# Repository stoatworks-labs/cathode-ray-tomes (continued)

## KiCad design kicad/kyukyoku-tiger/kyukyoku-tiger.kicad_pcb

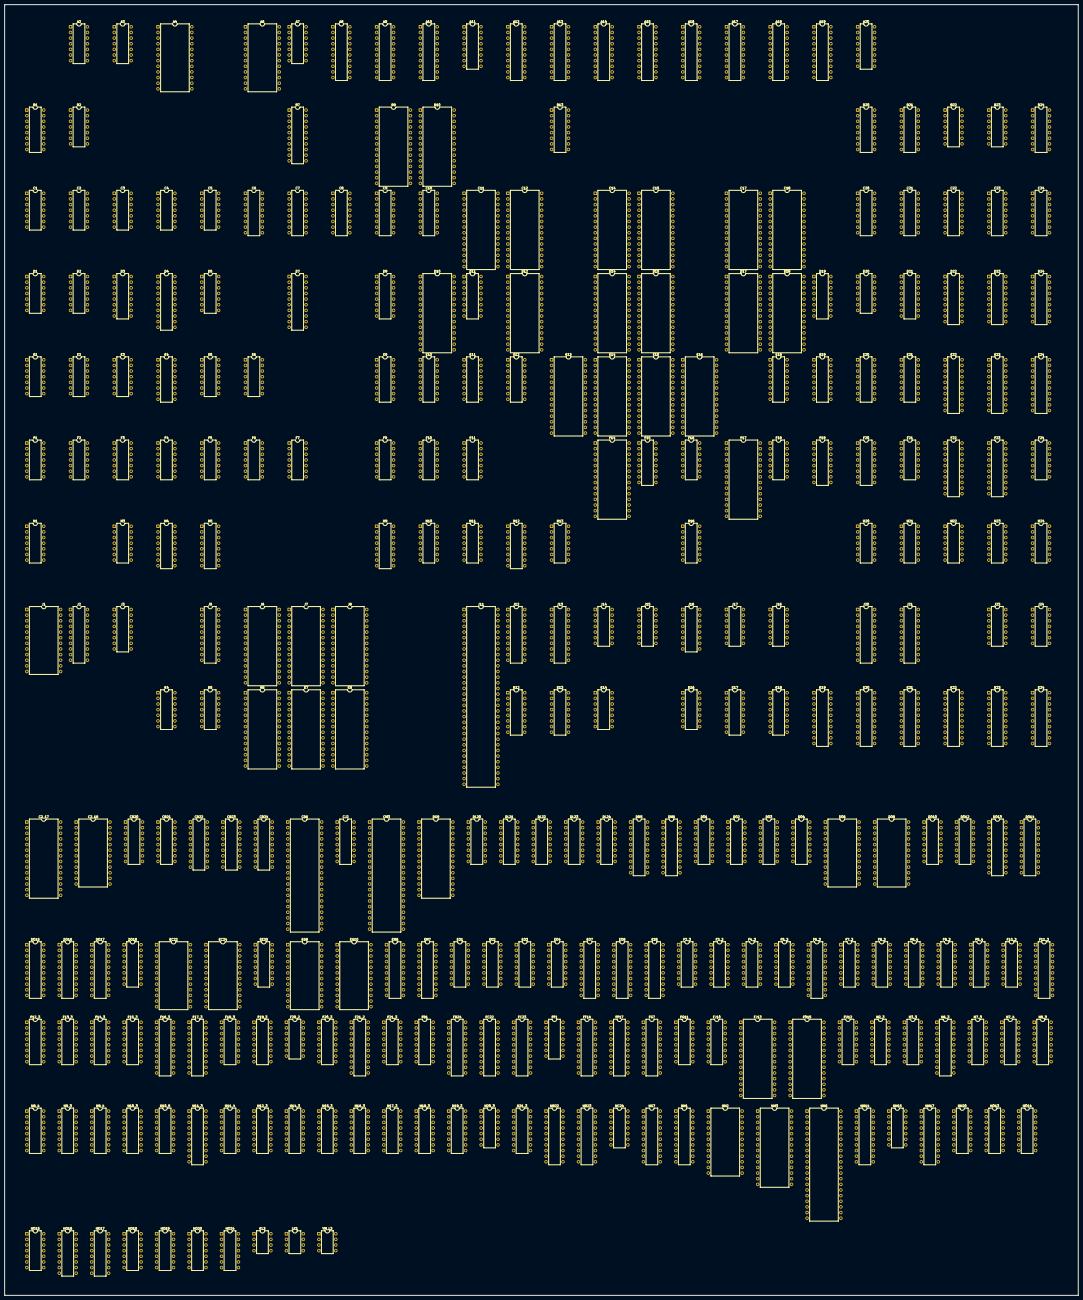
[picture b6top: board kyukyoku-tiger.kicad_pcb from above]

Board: 2 copper layers, 483.7 x 581.5 mm, 292 parts (0 on the bottom side), 1167 nets, no tracks yet.

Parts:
A2, A3: 74LS04; DIP-14_W7.62mm
A4, A6: M2732AF1; DIP-24_W15.24mm
A7: 74LS74; DIP-14_W7.62mm
A8, A9, A10, A12, A13, A14, A15, A16, A17, A18, A19: 74LS299; DIP-20_W7.62mm
A11, A20: 74LS157; DIP-16_W7.62mm
B1: 74LS163; DIP-16_W7.62mm
B2: 74LS04; DIP-14_W7.62mm
B7: 74LS245; DIP-20_W7.62mm
B9, B10: 27512; DIP-28_W15.24mm
B13: 74LS157; DIP-16_W7.62mm
B20, B21: 74LS153; DIP-16_W7.62mm
B22, B23: 74LS32; DIP-14_W7.62mm
B24: N82S123N; DIP-16_W7.62mm
C1: 74LS74; DIP-14_W7.62mm
C2, C4: 74LS04; DIP-14_W7.62mm
C2_17, C11, C12, C14, C15: 6264SL; DIP-28_W15.24mm
C2_18: RAM_2016; DIP-24_W15.24mm
C3, C5: 74LS393; DIP-14_W7.62mm
C6, C7, C8, C9, C10: 74LS157; DIP-16_W7.62mm
C17, C18: 27256; DIP-28_W15.24mm
C20, C21, C22: 74LS153; DIP-16_W7.62mm
C23, C24: 74LS174; DIP-16_W7.62mm
CB20, CB21: 74LS157; DIP-16_W7.62mm
CB22, CB23, CB24: MBM2148; DIP-18_W7.62mm
CD6: DSP32010; DIP-40_W15.24mm
CJ2: 74LS163; DIP-16_W7.62mm
CM3: MC6845; DIP-40_W15.24mm
D1, D20: 74LS32; DIP-14_W7.62mm
D2: 74LS08; DIP-14_W7.62mm
D3, D21: 74LS175; DIP-16_W7.62mm
D4: 74LS245; DIP-20_W7.62mm
D5: 74LS393; DIP-14_W7.62mm
D7: 74LS374; DIP-20_W7.62mm
D9: 74LS163; DIP-16_W7.62mm
D10, D12, D14, D15, D17, D18: 27256; DIP-28_W15.24mm
D11: 74LS669; DIP-16_W7.62mm
D19: 74LS169; DIP-16_W7.62mm
D22, D23, D24: MBM2148; DIP-18_W7.62mm
DG9: 27512; DIP-28_W15.24mm
DL20, DL21, DL22, DL23, DL24: 74LS157; DIP-16_W7.62mm
DM5: 74LS245; DIP-20_W7.62mm
DM6: 74LS374; DIP-20_W7.62mm
DO1, DO10: 74LS163; DIP-16_W7.62mm
DO2: N82S123N; DIP-16_W7.62mm
DO3, DO4: 82S126-9; DIP-16_W7.62mm
DO6, DO8: RAM_2016; DIP-24_W15.24mm
DO12: 74LS367; DIP-16_W7.62mm
DO13, DO14, DO15, DO16, DO17: 74LS374; DIP-20_W7.62mm
DO18: 74LS174; DIP-16_W7.62mm
E1, E6: 74LS08; DIP-14_W7.62mm
E2, E3, E5: 74LS74; DIP-14_W7.62mm
E4: 74LS139; DIP-16_W7.62mm
E9, E10, E11, E12: 74LS174; DIP-16_W7.62mm
E13, E14, E15, E16: LC3664; DIP-28_W15.24mm
E18: N82S123N; DIP-16_W7.62mm
E19: 74LS169; DIP-16_W7.62mm
E20, E21: 74LS157; DIP-16_W7.62mm
E22, E24: 74LS373; DIP-20_W7.62mm
E23: 74LS374; DIP-20_W7.62mm
EC22, EC24: CXK5816; DIP-24_W15.24mm
EE20: 74LS174; DIP-16_W7.62mm
EG9, EG10: CXK5816; DIP-24_W15.24mm
EM6, EM7: 74LS245; DIP-20_W7.62mm
EO1, EO2: 74LS175; DIP-16_W7.62mm
EO3: 74LS174; DIP-16_W7.62mm
EO4: 74LS138; DIP-16_W7.62mm
EO7, EO8: 74LS245; DIP-20_W7.62mm
ES5: 74LS245; DIP-20_W7.62mm
F1, F21: 74LS04; DIP-14_W7.62mm
F2, F11, F24: 74LS74; DIP-14_W7.62mm
F2_3, F8_4, F9_4, F14_3, F21_3: 74LS174; DIP-16_W7.62mm
F3: 74LS393; DIP-14_W7.62mm
F3_3, F4_3, F5_3, F8_3, F9_3, F10_3, F15_3: 74LS669; DIP-16_W7.62mm
F4: 74HC164; DIP-14_W7.62mm
F5, F7, F10, F16: 74LS32; DIP-14_W7.62mm
F6, F18, F20_2: 74LS08; DIP-14_W7.62mm
F6_3, F11_3, F16_3, F17_3: 74LS273; DIP-20_W7.62mm
F7_3, F12_3, F13_3, F18_3, F19_3, F20_3: 74LS157; DIP-16_W7.62mm
F9: 74LS10; DIP-14_W7.62mm
F14, F17: 27512; DIP-28_W15.24mm
F15: 74LS175; DIP-16_W7.62mm
F19: 74LS169; DIP-16_W7.62mm
F20: 74LS139; DIP-16_W7.62mm
F21_2: 74LS244; DIP-20_W7.62mm
F22: 74LS373; DIP-20_W7.62mm
F23: 74LS374; DIP-20_W7.62mm
FB1: 74LS157; DIP-16_W7.62mm
FB24: 74LS373; DIP-20_W7.62mm
FC22, FC23: 74LS245; DIP-20_W7.62mm
FF1: 74LS08; DIP-14_W7.62mm
FF14, FF17: 74LS245; DIP-20_W7.62mm
FG7: 74LS245; DIP-20_W7.62mm
FG11: 74LS175; DIP-16_W7.62mm
FJ10: 74LS163; DIP-16_W7.62mm
FJ13: 27512; DIP-28_W15.24mm
FO15: 27512; DIP-28_W15.24mm
FU12: 74LS138; DIP-16_W7.62mm
H1, H13, H20_3: 74LS74; DIP-14_W7.62mm
H2_3, H14_3, H21_3: 74LS174; DIP-16_W7.62mm
H3: 74LS04; DIP-14_W7.62mm
H3_3, H4, H5, H8_3, H9_3, H10_3, H15_3, H16_3, H17_3, H18_3, H19_3: 74LS669; DIP-16_W7.62mm
H6_3, H11_3: 74LS273; DIP-20_W7.62mm
H7_3, H12_3: 74LS157; DIP-16_W7.62mm
H7_4, H8_4, H9_4, H10_5, H11_4: 74LS161; DIP-16_W7.62mm
H9: 74LS139; DIP-16_W7.62mm
H10, H21: 74LS86; DIP-14_W7.62mm
H11: 74LS02; DIP-14_W7.62mm
H12: 74LS138; DIP-16_W7.62mm
H16: 74LS32; DIP-14_W7.62mm
H20, H23: 74LS08; DIP-14_W7.62mm
H22: 74LS10; DIP-14_W7.62mm
H24: 74LS20; DIP-14_W7.62mm
HB22, HB23: 74LS374; DIP-20_W7.62mm
HC24: 74LS08; DIP-14_W7.62mm
HG7: 74LS245; DIP-20_W7.62mm
HH1: 74LS244; DIP-20_W7.62mm
HH2: CXK5816; DIP-24_W15.24mm
HH3: 27256; DIP-28_W15.24mm
HH6: Z80CPU; DIP-40_W15.24mm
HH14, HH17: 74LS245; DIP-20_W7.62mm
HH15: 74LS10; DIP-14_W7.62mm
HH20: 74LS138; DIP-16_W7.62mm
HO13, HO14, HO16, HO17: 74LS166; DIP-16_W7.62mm
HO15: 74LS74; DIP-14_W7.62mm
HO18, HO19: 74LS32; DIP-14_W7.62mm
HO20: 74LS08; DIP-14_W7.62mm
HO24: 74LS20; DIP-14_W7.62mm
J1: YM3812; DIP-24_W15.24mm
J2, J12, J13: 74LS245; DIP-20_W7.62mm
J3: 74LS139; DIP-16_W7.62mm
J5: 74LS244; DIP-20_W7.62mm
J6, J7: 27512; DIP-28_W15.24mm
J8: LC3664; DIP-28_W15.24mm
J11: 68000D; DIP-64_W15.24mm
J14: 74LS03; DIP-14_W7.62mm
J15: 74LS04; DIP-14_W7.62mm
J16: 74LS133; DIP-16_W7.62mm
J17, J18, J23, J24: 74LS08; DIP-14_W7.62mm
J20, J21: 74LS240; DIP-20_W7.62mm
K4: 74LS74; DIP-14_W7.62mm
K5, K14: 74LS32; DIP-14_W7.62mm
K6, K7: 27512; DIP-28_W15.24mm
K8: LC3664; DIP-28_W15.24mm
K12, K13: 74LS138; DIP-16_W7.62mm
K16: 74LS14; DIP-14_W7.62mm
K17, K18: 74LS259; DIP-16_W7.62mm
K19, K20, K21, K22: 74LS240; DIP-20_W7.62mm
K23, K24: 74LS374; DIP-20_W7.62mm
KL3: HA17558; DIP-8_W7.62mm
LK1: uPC1241H; DIP-8_W7.62mm
YM_L3: YM3014; DIP-8_W7.62mm

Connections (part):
/1J16: J16.1, K5.8
/AO2_68: F20.1, J16.7, K12.13
/AO4_68: HH20.4, J16.13, K12.11
/BOT13: F6_3.11, H1.11, H9.4
/BOT16: H1.3, H6_3.11, H9.5
/BOT20: F2_3.9, H2_3.9, H9.6
/BOT21: B9.8, B10.8, DG9.8, H5.12
/BOT22: B9.9, B10.9, DG9.9, H5.13
/BOT23: B9.10, B10.10, DG9.10, H5.14
/BOT24: F5_3.12, F7_3.1, F9.9, F10.9, FB1.1, H7_3.1, H11.12
/BOT25: F5_3.13, H10.10
/BOT26: F5_3.14, H10.4
/BOT28: F1.11, H7_3.9
/BUSD0: CM3.33, DM5.9, ES5.11
/BUSD1: CM3.32, D2.1, DM5.8, ES5.12
/BUSD2: CM3.31, DM5.7, ES5.13
/BUSD3: CM3.30, DM5.6, ES5.14
/BUSD4: CM3.29, DM5.5, ES5.15
/BUSD5: CM3.28, DM5.4, ES5.16
/BUSD6: CM3.27, DM5.3, ES5.17
/BUSD7: CM3.26, DM5.2, ES5.18
/CE: D20.8, FF14.19, HH14.19
/CK3p5: B2.6, D3.9, F1.3, HH6.6, J1.24, K4.3, K4.11
/CK14: B2.4, CD6.8
/CLKB: B1.14, B2.3, CJ2.2, D19.2, DO1.2, E19.2, EO1.9, EO2.9, F7.10, F19.2, H3.1, HO13.7, HO14.7, HO16.7, HO17.7
/CLK_X: A8.12, A9.12, A10.12, A12.12, A13.12, A14.12, A15.12, A16.12, A17.12, A18.12, A19.12, B2.2, C23.9, C24.9, D1.2, D21.9, F3_3.2, F8_3.2, F9_3.2, F10_3.2, F15.9, FG11.9, H16.10, H16.13, H17_3.2, H18_3.2, H19_3.2, K23.11, K24.11
/CNT12: B2.13, H3.13
/CNT14: B1.12, B2.5
/CNT16: B1.11, B2.9
/CNT17: C2.10, F2.13, H9_4.9, H11_4.9
/CNT18: C2.8, E6.5, F2.3, F3.13, F4.8, H7_4.9, H8_4.9, H9_4.2, H10_5.9, H11_4.2, HO15.3
/CNT50: F2.2, F5.4, F6.3, K19.4, K20.4
/CNTA46: C4.13, F2.12, F5.12, J5.18
/CNTA47: FF1.12, K12.12
/CNTA50: FF1.11, J16.14
/COL0: EC24.9, FC23.2, HC24.1
/COL1: EC24.10, FC23.3, HC24.4
/COL2: EC24.11, FC23.4, J24.13
/COL3: EC24.13, FC23.5, J24.10
/COL4: EC24.14, FC23.6, HC24.10
/COL5: EC24.15, FC23.7, J24.1
/COL6: EC24.16, FC23.8, J24.4
/COL7: EC24.17, FC23.9
/COL8: EC22.9, FC22.2, H23.10
/COL9: EC22.10, FC22.3, H23.13
/COL10: EC22.11, FC22.4, J23.13
/COL11: EC22.13, FC22.5, H23.1
/COL12: EC22.14, FC22.6, J23.10
/COL13: EC22.15, FC22.7, H23.4
/COL14: EC22.16, FC22.8, J23.1
/COL15: EC22.17, FC22.9, J23.4
/COLMIX: DL22.1, DL23.1, DL24.1, H23.2, H23.5, H23.9, H23.12, HC24.2, HC24.5, HC24.9, J18.11, J23.2, J23.5, J23.9, J23.12, J24.2, J24.5, J24.9, J24.12
/COLMIX_AB: D20.5, F10.8, F21.13, FC22.1, FC23.1, FG7.19, HG7.19
/CPU_A0: EM7.2, HH2.8, HH3.10, HH6.30, J1.4
/CPU_A1: EM7.3, HH2.7, HH3.9, HH6.31
/CPU_A2: EM7.4, HH2.6, HH3.8, HH6.32
/CPU_A3: EM7.5, HH2.5, HH3.7, HH6.33
/CPU_A4: EM7.6, H12.1, HH2.4, HH3.6, HH6.34
/CPU_A5: EM7.7, H12.2, HH2.3, HH3.5, HH6.35
/CPU_A6: EM7.8, H12.3, HH2.2, HH3.4, HH6.36
/CPU_A7: EM7.9, HH2.1, HH3.3, HH6.37
/CPU_A8: EM6.2, HH2.23, HH3.25, HH6.38
/CPU_A9: EM6.3, HH2.22, HH3.24, HH6.39
/CPU_A10: EM6.4, HH2.19, HH3.21, HH6.40
/CPU_A11: EM6.5, HH3.23, HH6.1
/CPU_A12: EM6.6, HH3.2, HH6.2
/CPU_A13: EM6.7, HH3.26, HH6.3
/CPU_A14: EM6.8, HH3.27, HH6.4
/CPU_A15: EM6.9, HH6.5, J3.2
/CPU_AA1: F1.5, F10.10, F10.12, F20.12
/CPU_AB0: B7.9, C6.3, CM3.24, DL22.2, F20.2, F20.14, HH20.1
/CPU_AB2: B7.2, C7.13, DL23.14
/CPU_AB3: B7.7, C6.10, DL22.11, HH20.3
/CPU_AB4: B7.5, C7.3, DL23.2
/CPU_AB5: B7.4, C7.6, DL23.5
/CPU_AB6: B7.6, C6.13, DL22.14
/CPU_AB8: B7.3, C7.10, C8.3, DL23.11
/CPU_AB9: B7.8, C6.6, C8.6, DL22.5, F20.3, F20.13, HH20.2
/CPU_AB10: C8.10, DL24.11
/CPU_BB0: F16.10, F16.12, F20.11, F21.11
/CPU_D0: ES5.9, HH2.9, HH3.11, HH6.14, J2.2
/CPU_D1: ES5.8, HH2.10, HH3.12, HH6.15, J2.3
/CPU_D2: ES5.7, HH2.11, HH3.13, HH6.12, J2.4
/CPU_D3: ES5.6, HH2.13, HH3.15, HH6.8, J2.5
/CPU_D4: ES5.5, HH2.14, HH3.16, HH6.7, J2.9
/CPU_D5: ES5.4, HH2.15, HH3.17, HH6.9, J2.8
/CPU_D6: ES5.3, HH2.16, HH3.18, HH6.10, J2.7
/CPU_D7: ES5.2, HH2.17, HH3.19, HH6.13, J2.6
/CPU_DB0: F6_3.14, F11_3.14, H6_3.17, H11_3.17, H20_3.2, H20_3.12, H21_3.6, HH14.13, HH17.13
/CPU_DB2: F2_3.6, F6_3.4, F11_3.4, F11_3.18, F14_3.6, H6_3.7, H11_3.7, HH14.16, HH17.16
/CPU_DB3: EO7.4, H21_3.14
/CPU_DB5: F2_3.3, F6_3.3, F11_3.3, F14_3.3, H6_3.8, H11_3.8, HH14.18, HH17.18
/CPU_DB6: EO7.2, H21_3.13
/CPU_DB8: F2_3.4, F6_3.18, F14_3.4, H6_3.13, H11_3.13, H21_3.11, HH14.17, HH17.17
/CPU_DB10: F2_3.14, F6_3.17, F11_3.17, F14_3.14, H6_3.14, H11_3.14, HH14.15, HH17.15
/CPU_DB11: EO7.5, F2_3.13, F4_3.2, F5_3.2, F6_3.7, F11_3.7, F14_3.13, H6_3.4, H11_3.4, HH14.14, HH17.14
/CPU_DB13: F6_3.8, F11_3.8, H2_3.3, H6_3.3, H11_3.3, H14_3.3, HH14.12, HH17.12
/CPU_DB14: EO7.8, F6_3.13, F11_3.13, H2_3.4, H6_3.18, H11_3.18, H14_3.4, HH14.11, HH17.11
/CPU_NXP1: B7.11, D7.2, EM7.11, J6.10, J7.10, J8.10, J11.29, K6.10, K7.10, K8.10
/CPU_NXP2: B7.12, D7.5, EM7.12, J6.9, J7.9, J8.9, J11.30, K6.9, K7.9, K8.9
/CPU_NXP3: B7.13, D7.6, EM7.13, J6.8, J7.8, J8.8, J11.31, K6.8, K7.8, K8.8
/CPU_NXP4: B7.14, D7.9, EM7.14, J6.7, J7.7, J8.7, J11.32, K6.7, K7.7, K8.7
/CPU_NXP5: B7.15, D7.12, EM7.15, J6.6, J7.6, J8.6, J11.33, K6.6, K7.6, K8.6
/CPU_NXP6: B7.16, D7.15, EM7.16, J6.5, J7.5, J8.5, J11.34, K6.5, K7.5, K8.5
/CPU_NXP7: B7.17, D7.16, EM7.17, J6.4, J7.4, J8.4, J11.35, K6.4, K7.4, K8.4
/CPU_NXP8: B7.18, D7.19, EM7.18, J6.3, J7.3, J8.3, J11.36, K6.3, K7.3, K8.3
/CPU_NXP9: DM6.19, EM6.18, J6.25, J7.25, J8.25, J11.37, K6.25, K7.25, K8.25
/CPU_NXP10: DM6.16, EM6.17, J6.24, J7.24, J8.24, J11.38, K6.24, K7.24, K8.24
/CPU_NXP11: DM6.15, EM6.16, J6.21, J7.21, J8.21, J11.39, K6.21, K7.21, K8.21
/CPU_NXP12: DM6.12, EM6.15, J6.23, J7.23, J8.23, J11.40, K6.23, K7.23, K8.23
/CPU_NXP13: DM6.9, EM6.14, J6.2, J7.2, J8.2, J11.41, K6.2, K7.2, K8.2
/CPU_NXP14: EM6.13, J6.26, J7.26, J11.42, K6.26, K7.26
/CPU_NXP15: EM6.12, J6.27, J7.27, J11.43, K6.27, K7.27
/CPU_NXP16: DM6.6, J6.1, J11.44, K6.1, K13.1
/CPU_NXP17: DM6.5, J11.45, K13.2
/CPU_NXP18: DM6.2, J11.46, K13.3, K14.9
/DB0: FC23.18, J12.18
/DB1: FC23.17, J12.17
/DB2: FC23.16, J12.16
/DB3: FC23.15, J12.15
/DB4: FC23.14, J12.14
/DB5: FC23.13, J12.13
/DB6: FC23.12, J12.12
/DB7: FC23.11, J12.11
/DB8: FC22.18, J13.18
/DB9: FC22.17, J13.17
/DB10: FC22.16, J13.16
/DB11: FC22.15, J13.15
/DB12: FC22.14, J13.14
/DB13: FC22.13, J13.13
/DB14: FC22.12, J13.12
/DB15: FC22.11, J13.11
/EPROM0: J6.11, J7.11, J8.11, J11.5, J12.2
/EPROM1: J6.12, J7.12, J8.12, J11.4, J12.3
/EPROM2: J6.13, J7.13, J8.13, J11.3, J12.4
/EPROM3: J6.15, J7.15, J8.15, J11.2, J12.5
/EPROM4: J6.16, J7.16, J8.16, J11.1, J12.6
/EPROM5: J6.17, J7.17, J8.17, J11.64, J12.7
/EPROM6: J6.18, J7.18, J8.18, J11.63, J12.8
/EPROM7: J6.19, J7.19, J8.19, J11.62, J12.9
/EPROM8: D4.9, J11.61, K6.11, K7.11, K8.11
/EPROM9: D4.8, J11.60, K6.12, K7.12, K8.12
/EPROM10: D4.7, J11.59, K6.13, K7.13, K8.13
/EPROM11: D4.6, J11.58, K6.15, K7.15, K8.15
/EPROM12: D4.5, J11.57, K6.16, K7.16, K8.16
/EPROM13: D4.4, J11.56, K6.17, K7.17, K8.17, K12.1
/EPROM14: D4.3, J11.55, K6.18, K7.18, K8.18, K12.2
/EPROM15: D4.2, J11.54, K6.19, K7.19, K8.19, K12.3
/E_68: CM3.23, J11.20
/E_F20: F20.15, K12.7
/FLIP: F9.13, H10.2, H10.5, H10.9, H10.13, H21.9, H21.13, H22.9, HH15.9, J15.3, K17.7
/GFXA0: A11.4, B20.6, B23.1
/GFXA1: A11.7, B20.10, B23.2
/GFXA2: A11.9, B21.6, B23.13
/GFXA3: B21.10, E11.12
/GFXA4: C20.6, E11.10
/GFXA5: C20.10, E11.7
/GFXA6: C21.6, E11.5
/GFXA7: C21.10, E11.2
/GFXA_A0: EG9.8, EG10.8, FB1.4
/GFXA_A1: EG9.7, EG10.7, FB1.7
/GFXA_A2: EG9.6, EG10.6, FB1.12
/GFXA_A3: EG9.5, EG10.5, FB1.9
/GFXA_A4: EG9.4, EG10.4, F7_3.4
/GFXA_A5: EG9.3, EG10.3, F7_3.7
/GFXA_A6: EG9.2, EG10.2, F7_3.12
/GFXA_A7: EG9.1, EG10.1, F7_3.9
/GFXA_A8: EG9.23, EG10.23, H7_3.4
/GFXA_A9: EG9.22, EG10.22, H7_3.7
/GFXA_A10: EG9.19, EG10.19, H7_3.12
/GFXC0: A20.4, B20.4, B22.1
/GFXC1: A20.7, B20.12, B22.2
/GFXC2: A20.9, B21.4, B22.5
/GFXC3: A20.12, B21.12, B22.4
/GFXC4: C20.4, EE20.10
/GFXC5: C20.12, EE20.7
/GFXC6: C21.4, EE20.5
/GFXD0: B13.4, B20.3, C21.12, EE20.2
/GFXD1: B13.7, B20.13
/GFXD2: B13.9, B21.3
/GFXD3: B13.12, B21.13
/GFXD4: C20.3, E12.10
/GFXD5: C20.13, E12.7
/GFXD6: C21.3, E12.5
/GFXD7: C21.13, E12.2
/MAIN: F10.11, J16.2
/MID12: E13.23, E14.23, H9.12
/MID13: E13.21, E14.21, F11_3.11, H13.11
/MID14: E13.24, E14.24
/MID15: E13.25, E14.25, H9.11
/MID16: E13.3, E14.3, H11_3.11, H13.3
/MID17: E13.4, E14.4
/MID18: E13.5, E14.5
/MID19: E13.6, E14.6, H9.9
/MID20: D10.8, D12.8, D14.8, D15.8, E13.7, E14.7, F14_3.9, H14_3.9
/MID21: D10.9, D12.9, D14.9, D15.9, E13.8, E14.8, H10_3.12
/MID22: D10.10, D12.10, D14.10, D15.10, E13.9, E14.9, H10_3.13
/MID23: E13.10, E14.10, H10_3.14, HH15.13
/MID24: F10_3.12, F12_3.1, F13_3.1, F16.9, F21.9, H10.1, H11.8, H12_3.1
/MID25: F10_3.13, H10.12
/MISC_OA4: E13.2, E14.2, K17.9
/MIS_O3A: H16.1, J5.12
/M_SI0: H16.9, HH15.4, HH15.5, HH15.10, HH15.11, HH15.12
/M_SI01: H16.12, H22.4, H22.5, H22.10, H22.11, H22.12
/OBJDRAW0: EO8.2, F16_3.3, F17_3.3, F21_3.3, FF14.18, FF17.18, H1.2, H1.12, H2_3.14, H13.2, H13.12, H14_3.14, HG7.18, J13.2
/OBJDRAW1: EO8.3, F16_3.18, F17_3.18, F21_3.14, FF14.17, FF17.17, H2_3.13, H14_3.13, J13.3
/OBJDRAW2: EO8.4, F16_3.4, F17_3.4, F21_3.4, FF14.16, FF17.16, H2_3.11, H14_3.11, J13.4
/OBJDRAW3: EO8.5, F16_3.17, F17_3.17, F21_3.13, FF14.15, FF17.15, H14_3.6, J13.5
/OBJDRAW4: EO8.6, F16_3.7, F17_3.7, F21_3.6, FF14.14, FF17.14, J13.6
/OBJDRAW5: EO8.7, F16_3.14, F17_3.14, F21_3.11, FF14.13, FF17.13, J13.7
/OBJDRAW6: EO8.8, F16_3.8, F17_3.8, FF14.12, FF17.12, H21_3.3, J13.8
/OBJDRAW7: EO8.9, F16_3.13, F17_3.13, FF14.11, FF17.11, H21_3.4, J13.9
/OBJPXL0: B20.5, B22.13, HB22.9
/OBJPXL1: B20.11, B22.12, HB22.6
/OBJPXL2: B21.5, B22.10, HB22.5
/OBJPXL3: B21.11, B22.9, HB22.2
/OBJPXL4: C20.5, HB22.12
/OBJPXL5: C20.11, HB22.15
/OBJPXL6: C21.5, HB22.16
/OBJPXL7: C21.11, HB22.19
/OBJPXL8: B24.12, HB23.12
/OBJPXL9: B24.13, HB23.15
/OBJPXL10: C22.11, HB23.16
/OBJPXL11: C22.5, HB23.19
/OO2: D20.10, D20.12, F20.10, F21.1
/PXL0: C23.15, DL22.3
/PXL1: C23.12, DL22.6
/PXL2: C23.2, DL22.10
/PXL3: C23.5, DL22.13
/PXL4: C23.7, DL23.3
/PXL5: C24.12, DL23.6
/PXL6: C24.15, DL23.10
/PXL7: C23.10, DL23.13
/PXL8: C24.2, DL24.3
/PXL9: C24.5, DL24.6
/PXL10: C24.7, DL24.10
/RAM_A3: D10.7, D12.7, D14.7, D15.7, E13.11, FF14.2
/RAM_A4: D10.6, D12.6, D14.6, D15.6, E13.12, FF14.3
/RAM_A5: D10.5, D12.5, D14.5, D15.5, E13.13, FF14.4
/RAM_A6: D10.4, D12.4, D14.4, D15.4, E13.15, FF14.5
/RAM_A7: D10.3, D12.3, D14.3, D15.3, E13.16, FF14.6
/RAM_A8: D10.25, D12.25, D14.25, D15.25, E13.17, FF14.7
/RAM_A9: D10.24, D12.24, D14.24, D15.24, E13.18, FF14.8
/RAM_A10: D10.21, D12.21, D14.21, D15.21, E13.19, FF14.9
/RAM_A11: D10.23, D12.23, D14.23, D15.23, E14.11, HH14.2
/RAM_A12: D10.2, D12.2, D14.2, D15.2, E14.12, HH14.3
/RAM_A13: D10.26, D12.26, D14.26, D15.26, E14.13, HH14.4
/RAM_A14: D10.27, D12.27, D14.27, D15.27, E14.15, HH14.5
/RAM_AA3: C17.7, C18.7, D17.7, D18.7, E15.11, FF17.2
/RAM_AA4: C17.6, C18.6, D17.6, D18.6, E15.12, FF17.3
/RAM_AA5: C17.5, C18.5, D17.5, D18.5, E15.13, FF17.4
/RAM_AA6: C17.4, C18.4, D17.4, D18.4, E15.15, FF17.5
/RAM_AA7: C17.3, C18.3, D17.3, D18.3, E15.16, FF17.6
/RAM_AA8: C17.25, C18.25, D17.25, D18.25, E15.17, FF17.7
/RAM_AA9: C17.24, C18.24, D17.24, D18.24, E15.18, FF17.8
/RAM_AA10: C17.21, C18.21, D17.21, D18.21, E15.19, FF17.9
/RAM_AA11: C17.23, C18.23, D17.23, D18.23, E16.11, HH17.2
/RAM_AA12: C17.2, C18.2, D17.2, D18.2, E16.12, HH17.3
/RAM_AA13: C17.26, C18.26, D17.26, D18.26, E16.13, HH17.4
/RAM_AA14: C17.27, C18.27, D17.27, D18.27, E16.15, HH17.5
/R_~WE: EC22.21, EC24.21, H16.3
/TMB19: A11.1, A20.1, B13.1, F3_3.1, F4_3.1, F5_3.1, F8_3.1, F9.3, F9_3.1, F10_3.1, F15_3.1, H3_3.1, H4.1, H5.1, H8_3.1, H9_3.1, H10_3.1, H15_3.1, H16_3.1, H17_3.1, H18_3.1, H19_3.1, H22.3, HH15.3, J15.4
/TOP1: E15.23, E16.23
/TOP2: E15.21, E16.21
/TOP3: C17.8, C18.8, D17.8, D18.8, E15.24, E16.24
/TOP4: C17.9, C18.9, D17.9, D18.9, E15.25, E16.25
/TOP5: C17.10, C18.10, D17.10, D18.10, E15.3, E16.3
/TOP6: E15.4, E16.4, H22.13
/TOP7: E15.5, E16.5, H21.10
/TOP8: E15.6, E16.6, H21.12
/TOP9: E15.7, E16.7
/TOP10: E15.8, E16.8
/TOP11: E15.9, E16.9
/TOP12: E15.10, E16.10
/TOP13: F17_3.11, F20.4, H20_3.11
/TOP16: F16_3.11, F20.5, H20_3.3
/TOP20: F20.6, F21_3.9, H21_3.9
/TOP24: D20.9, F18_3.1, F19_3.1, F20_3.1, F21.3, H11.5, H17_3.14
/UDB: FC22.19, FC23.19, H16.4, J16.4, J17.4, K13.10
/VPP_A: C17.1, C18.1, D17.1, D18.1, K17.10
/Y0: J1.10, J2.18, J20.18, J21.18, K18.13, K19.12
/Y1: J1.11, J2.17, J20.16, J21.16, K18.1, K19.14
/Y2: J1.13, J2.16, J20.14, J21.14, K18.2, K19.5
/Y3: J1.14, J2.15, J20.12, J21.12, K18.3, K19.7
/Y4: J1.15, J2.11, J20.9, J21.9, K19.9
/Y5: J1.16, J2.12, J20.7, J21.7, K19.3
/Y6: J1.17, J2.13, J20.5, J21.5, K19.18
/Y7: J1.18, J2.14, J20.3, J21.3, K19.16
/boardb/A00: C3.3, DO3.5, DO4.5
/boardb/A01: C3.4, DO3.6, DO4.6
/boardb/A02: C3.5, DO3.7, DO4.7
/boardb/A03: C3.6, C3.13, DO3.4, DO4.4
/boardb/A04: C3.11, DO3.3, DO4.3
/boardb/A05: C3.10, DO3.2, DO4.2
/boardb/A06: C3.9, DO3.1, DO4.1
/boardb/A07: C3.8, DO3.15, DO4.15
/boardb/AA8: CB22.16, CB23.16, CB24.16, E21.4
/boardb/AB8: D22.16, D23.16, D24.16, E20.4
/boardb/BUFA0: DL20.3, DL21.3, E19.14
/boardb/BUFA1: DL20.6, DL21.6, E19.13
/boardb/BUFA2: DL20.10, DL21.10, E19.12
/boardb/BUFA3: CB20.13, CB21.13, D19.11
/boardb/BUFA4: CB20.10, CB21.10, D19.12
/boardb/BUFA5: CB20.6, CB21.6, D19.13
/boardb/BUFA6: CB20.3, CB21.3, D19.14
/boardb/BUFA7: DL20.13, DL21.13, E19.11
/boardb/CK: D9.2, D11.2, DO10.2, F6.8, FJ10.2
/boardb/CLKBUF: E22.11, E23.11, E24.11, F22.11, F23.11, FB24.11, HB22.11, HB23.11, HO13.15, HO14.15, HO16.15, HO17.15, HO18.8
/boardb/CLKCNT: C4.1, EO3.9, EO4.4, F8_4.9, F9_4.9, H3.12, H7_4.2, H8_4.2, H10_5.2, HO19.2, HO19.13
/boardb/CLKRA: DO18.9, F6.11
/boardb/D6: C2_17.11, DO16.9, F23.17
/boardb/D7: C2_17.12, DO16.12, E23.18, F23.18
/boardb/LBDC: C11.13, DO12.13, F19.3
/boardb/MIX0: C14.11, DO14.2, E23.3
/boardb/MIX1: C14.12, DO14.5, E23.4, F23.4
/boardb/MIX2: C14.13, DO14.6, E23.7, F23.7
/boardb/MIX3: C14.15, DO14.9, E23.8, F23.8
/boardb/MIX4: C14.16, DO14.12, E23.13, F23.13
/boardb/MIX5: C14.17, DO14.15, E23.14, F23.14
/boardb/MIX6: C14.18, DO14.16
/boardb/MRCLK0: EO3.2, EO4.1
/boardb/MRCLK1: EO3.5, EO4.3
/boardb/MRCLK2: C4.5, EO3.7
/boardb/MRCLK3: EO3.10, F5.1
/boardb/MRCLK4: C4.11, EO3.12
/boardb/MRCLK5: EO3.15, EO4.2
/boardb/MR_CLK1: DO13.11, DO15.11, EO4.14
/boardb/MR_CLK2: DO14.11, DO16.11, EO4.13
/boardb/MR_CLK3: DO17.11, EO4.12, F11.3
/boardb/MR_CLK4: E9.9, E10.9, EO4.11
/boardb/OBJA0: EO1.10, F14.10, F17.10, FJ13.10, FO15.10
/boardb/OBJA1: C11.16, DO12.3, F14.9, F17.9, FJ13.9, FO15.9
/boardb/OBJA2: C11.17, DO12.5, F14.8, F17.8, FJ13.8, FO15.8
/boardb/OBJA3: C11.18, DO12.9, F14.7, F17.7, FJ13.7, FO15.7
/boardb/OBJA4: C11.19, DO12.7, F14.6, F17.6, FJ13.6, FO15.6
/boardb/OBJA5: C12.11, DO13.2, F14.5, F17.5, FJ13.5, FO15.5
/boardb/OBJA6: C12.12, DO13.5, F14.4, F17.4, FJ13.4, FO15.4
/boardb/OBJA7: C12.13, DO13.6, F14.3, F17.3, FJ13.3, FO15.3
/boardb/OBJA8: C12.15, DO13.9, F14.25, F17.25, FJ13.25, FO15.25
/boardb/OBJA9: C12.16, DO13.12, F14.24, F17.24, FJ13.24, FO15.24
/boardb/OBJA10: C12.17, DO13.15, F14.21, F17.21, FJ13.21, FO15.21
/boardb/OBJA11: C12.18, DO13.16, F14.23, F17.23, FJ13.23, FO15.23
/boardb/OBJA12: C12.19, DO13.19, F14.2, F17.2, FJ13.2, FO15.2
/boardb/OBJA13: C15.11, DO15.5, F14.26, F17.26, FJ13.26, FO15.26
/boardb/OBJA14: C15.12, DO15.6, F14.27, F17.27, FJ13.27, FO15.27
/boardb/OBJA15: C15.13, DO15.9, F14.1, F17.1, FJ13.1, FO15.1
/boardb/OBJQ0: FJ13.11, HO13.2
/boardb/OBJQ1: FJ13.12, HO13.3
/boardb/OBJQ2: FJ13.13, HO13.4
/boardb/OBJQ3: FJ13.15, HO13.5
/boardb/OBJQ4: FJ13.16, HO13.10
/boardb/OBJQ5: FJ13.17, HO13.11
/boardb/OBJQ6: FJ13.18, HO13.12
/boardb/OBJQ7: FJ13.19, HO13.14
/boardb/OBJR0: F14.11, HO14.2
/boardb/OBJR1: F14.12, HO14.3
/boardb/OBJR2: F14.13, HO14.4
/boardb/OBJR3: F14.15, HO14.5
/boardb/OBJR4: F14.16, HO14.10
/boardb/OBJR5: F14.17, HO14.11
/boardb/OBJR6: F14.18, HO14.12
/boardb/OBJR7: F14.19, HO14.14
/boardb/OBJS0: FO15.11, HO16.2
/boardb/OBJS1: FO15.12, HO16.3
/boardb/OBJS2: FO15.13, HO16.4
/boardb/OBJS3: FO15.15, HO16.5
/boardb/OBJS4: FO15.16, HO16.10
/boardb/OBJS5: FO15.17, HO16.11
/boardb/OBJS6: FO15.18, HO16.12
/boardb/OBJS7: FO15.19, HO16.14
/boardb/OBJU0: F17.11, HO17.2
/boardb/OBJU1: F17.12, HO17.3
/boardb/OBJU2: F17.13, HO17.4
/boardb/OBJU3: F17.15, HO17.5
/boardb/OBJU4: F17.16, HO17.10
/boardb/OBJU5: F17.17, HO17.11
/boardb/OBJU6: F17.18, HO17.12
/boardb/OBJU7: F17.19, HO17.14
/boardb/OEA: CB21.1, DL21.1, E20.1, E22.1, E24.1, F20_2.2, F20_2.5, F20_2.10, F20_2.13, HO15.2, HO15.6
/boardb/OEB: CB20.1, DL20.1, E21.1, F18.2, F18.5, F18.10, F18.13, F22.1, FB24.1, H24.1, HO15.5, HO19.1, HO19.12, HO24.9
/boardb/PXLA0: CB22.14, E22.3, F21_2.3
/boardb/PXLA1: CB22.13, E22.4, F21_2.5
/boardb/PXLA2: CB22.12, E22.7, F21_2.7
/boardb/PXLA3: CB22.11, E22.8, F21_2.9
/boardb/PXLA4: CB23.14, E22.18, E23.2
/boardb/PXLA5: CB23.13, E22.17, E23.5
/boardb/PXLA6: CB23.12, E22.14, E23.6
/boardb/PXLA7: CB23.11, E22.13, E23.9
/boardb/PXLA8: CB24.14, E23.12, E24.13
/boardb/PXLA9: CB24.13, E23.15, E24.14
/boardb/PXLA10: CB24.12, E23.16, E24.17
/boardb/PXLA11: CB24.11, E23.19, E24.18
/boardb/PXLB0: D22.14, F21_2.18, F22.3
/boardb/PXLB1: D22.13, F21_2.16, F22.4
/boardb/PXLB2: D22.12, F21_2.14, F22.7
/boardb/PXLB3: D22.11, F21_2.12, F22.8
/boardb/PXLB4: D23.14, F22.18, F23.2
/boardb/PXLB5: D23.13, F22.17, F23.5
/boardb/PXLB6: D23.12, F22.14, F23.6
/boardb/PXLB7: D23.11, F22.13, F23.9
/boardb/PXLB8: D24.14, F23.12, FB24.13
/boardb/PXLB9: D24.13, F23.15, FB24.14
/boardb/PXLB10: D24.12, F23.16, FB24.17
/boardb/PXLB11: D24.11, F23.19, FB24.18
/boardb/Q0: DO12.1, DO12.15, DO13.1, DO14.1, DO15.1, DO16.1, DO17.1, EO1.2
/boardb/R04: C4.9, F5.8, F6.4
/boardb/RA0: C2_18.9, DO18.6
/boardb/RA1: C2_18.10, DO18.4
/boardb/RA2: C2_18.11, DO18.3, E18.3
/boardb/RA3: C2_18.13, DO18.13, E18.4
/boardb/RA4: C2_18.14, DO18.11, E18.5
/boardb/RAAD0: C2_17.10, C2_18.8, C9.4, C11.10, C12.10, C14.10, C15.10
/boardb/RAAD1: C2_17.9, C2_18.7, C9.7, C11.9, C12.9, C14.9, C15.9
/boardb/RAAD2: C2_17.8, C2_18.6, C9.9, C11.8, C12.8, C14.8, C15.8
/boardb/RAAD3: C2_17.7, C2_18.5, C9.12, C11.7, C12.7, C14.7, C15.7
/boardb/RAAD4: C2_17.6, C2_18.4, C10.4, C11.6, C12.6, C14.6, C15.6
/boardb/RAAD5: C2_17.5, C2_18.3, C10.7, C11.5, C12.5, C14.5, C15.5
/boardb/RAAD6: C2_17.4, C2_18.2, C10.9, C11.4, C12.4, C14.4, C15.4
/boardb/RAAD7: C2_17.3, C2_18.1, C10.12, C11.3, C12.3, C14.3, C15.3
/boardb/RAAD8: C2_17.25, C11.25, C12.25, C14.25, C15.25, DO18.7, E18.10
/boardb/RAAD9: C2_17.24, C11.24, C12.24, C14.24, C15.24, DO18.5, E18.11
/boardb/RAAD10: C2_17.21, C11.21, C12.21, C14.21, C15.21, DO18.2, E18.12
/boardb/RAAD11: C2_17.23, C11.23, C12.23, C14.23, C15.23, DO18.12, E18.13
/boardb/RAAD12: C2_17.2, C11.2, C12.2, C14.2, C15.2, DO18.10, E18.14
/boardb/RAM0: C6.4, DO6.8, DO8.8
/boardb/RAM1: C6.7, DO6.7, DO8.7
/boardb/RAM2: C6.9, DO6.6, DO8.6
/boardb/RAM3: C6.12, DO6.5, DO8.5
/boardb/RAM4: C7.4, DO6.4, DO8.4
/boardb/RAM5: C7.7, DO6.3, DO8.3
/boardb/RAM6: C7.9, DO6.2, DO8.2
/boardb/RAM7: C7.12, DO6.1, DO8.1
/boardb/RAM8: C8.4, DO6.23, DO8.23
/boardb/RAM9: C8.7, DO6.22, DO8.22
/boardb/RAM10: C8.9, DO6.19, DO8.19
/boardb/RAMAD8: DO6.9, DO13.3, DO14.3, EO7.18
/boardb/RAMAD9: DO6.10, DO13.4, DO14.4, EO7.17
/boardb/RAMAD10: DO6.11, DO13.7, DO14.7, EO7.16
/boardb/RAMAD11: DO6.13, DO13.8, DO14.8, EO7.15
/boardb/RAMAD12: DO6.14, DO13.13, DO14.13, EO7.14
/boardb/RAMAD13: DO6.15, DO13.14, DO14.14, EO7.13
/boardb/RAMAD14: DO6.16, DO13.17, DO14.17, EO7.12
/boardb/RAMAD15: DO6.17, DO13.18, DO17.3, E9.3, EO7.11
/boardb/RAMBUF0: C2_17.13, D19.3, DO17.2, E18.2
/boardb/RAMBUF1: C2_17.15, D19.4, DO17.5
/boardb/RAMBUF2: C2_17.16, D19.5, DO17.6
/boardb/RAMBUF3: C2_17.17, D19.6, DO17.9
/boardb/RAMBUF4: C2_17.18, DO17.12, E19.3
/boardb/RAMBUF5: C2_17.19, DO17.15, E19.4
/boardb/RAMBUF6: C11.12, DO17.16, E19.5
/boardb/RAMBUF7: C11.11, DO17.19, E19.6
/boardb/RAMD0: DO8.9, DO15.4, DO16.4, DO17.4, E9.14, E18.1, EO8.18
/boardb/RAMD1: DO8.10, DO15.7, DO17.7, E9.13, EO8.17
/boardb/RAMD2: DO8.11, DO15.8, DO16.8, DO17.8, E9.4, EO8.16
/boardb/RAMD3: DO8.13, DO15.13, DO16.13, DO17.13, E10.11, EO8.15
/boardb/RAMD4: DO8.14, DO15.14, DO17.14, E10.6, EO8.14
/boardb/RAMD5: DO8.15, DO17.17, E10.3, EO8.13
/boardb/RAMD6: DO8.16, DO17.18, E10.14, EO8.12
/boardb/RAMD7: DO8.17, E10.13, EO8.11, F11.2
/boardb/RAMDQ4: E10.12, FJ10.3
/boardb/RAMO3: C15.15, DO15.12
/boardb/RAMO4: C15.16, DO15.15
/boardb/RAMO7: C15.19, DO16.5, HO15.12
/boardb/RA~OE: C2_18.20, C4.8
/boardb/R~w: C2_17.27, C2_18.21, C11.27, C12.27, C14.27, C15.27, E18.15, F6.6
/boardb/SELECT: C4.3, C5.2, C5.12, C6.1, C7.1, C8.1, C9.1, C10.1, D5.2, E6.4, F5.2, F5.6
/boardb/TC: DO10.15, FJ10.7, FJ10.10
/boardb/TCA: D9.15, DO10.7, DO10.10
/boardb/U~D: D19.1, E19.1, F19.1, HO15.8
/boardb/bRD: C4.12, C8.13, EO7.1, EO8.1
/boardb/dump0: DL20.2, DL21.2, F9_4.2
/boardb/dump1: DL20.5, DL21.5, F9_4.5
/boardb/dump2: DL20.11, DL21.11, F8_4.5
/boardb/dump3: CB20.14, CB21.14, F9_4.15
/boardb/dump4: CB20.11, CB21.11, F9_4.12
/boardb/dump5: CB20.5, CB21.5, F9_4.7
/boardb/dump6: CB20.2, CB21.2, F9_4.10
/boardb/dump7: DL20.14, DL21.14, F8_4.2
/boardb/line_buffer/AA0: CB22.5, CB23.5, CB24.5, DL21.4
/boardb/line_buffer/AA1: CB22.6, CB23.6, CB24.6, DL21.7
/boardb/line_buffer/AA2: CB22.7, CB23.7, CB24.7, DL21.9
/boardb/line_buffer/AA3: CB21.12, CB22.4, CB23.4, CB24.4
/boardb/line_buffer/AA4: CB21.9, CB22.3, CB23.3, CB24.3
/boardb/line_buffer/AA5: CB21.7, CB22.2, CB23.2, CB24.2
/boardb/line_buffer/AA6: CB21.4, CB22.1, CB23.1, CB24.1
/boardb/line_buffer/AA7: CB22.17, CB23.17, CB24.17, DL21.12
/boardb/line_buffer/AB0: D22.5, D23.5, D24.5, DL20.4
/boardb/line_buffer/AB1: D22.6, D23.6, D24.6, DL20.7
/boardb/line_buffer/AB2: D22.7, D23.7, D24.7, DL20.9
/boardb/line_buffer/AB3: CB20.12, D22.4, D23.4, D24.4
/boardb/line_buffer/AB4: CB20.9, D22.3, D23.3, D24.3
/boardb/line_buffer/AB5: CB20.7, D22.2, D23.2, D24.2
/boardb/line_buffer/AB6: CB20.4, D22.1, D23.1, D24.1
/boardb/line_buffer/AB7: D22.17, D23.17, D24.17, DL20.12
/boardb/line_buffer/O4: E24.12, FB24.12, HB23.13
/boardb/line_buffer/O5: E24.15, FB24.15, HB23.14
/boardb/line_buffer/O6: E24.16, FB24.16, HB23.17
/boardb/line_buffer/O7: E24.19, FB24.19, HB23.18
/boardb/line_counter/CNNQ0: C10.3, H9_4.14
/boardb/line_counter/CNNQ1: C10.6, H9_4.13
/boardb/line_counter/CNNQ2: C10.10, H9_4.12
/boardb/line_counter/CNNQ3: C10.13, H9_4.11
/boardb/line_counter/CNQ0: C9.3, H11_4.14
/boardb/line_counter/CNQ1: C9.6, H11_4.13
/boardb/line_counter/CNQ2: C9.13, H11_4.12
/boardb/line_counter/CNQ3: C9.10, H11_4.11
/boardb/~CEP: D19.15, E19.7, E19.10
/boardb/~CET: E19.15, F19.7, F19.10
/boardb/~MR: C4.4, EO3.1
/boardb/~OBJCSAB: DO6.21, DO8.21, F5.11
/boardb/~OBJCS: EO7.19, EO8.19, F5.13, FF1.13, HO19.8
/boardb/~OE: CB22.10, CB23.10, CB24.10, E23.1, F21_2.19, HO20.11
/boardb/~PE: D9.9, D11.9, DO10.9, E5.6, FJ10.9
/boardb/~Q0: C2_17.22, C11.22, C12.22, C14.22, C15.22, EO1.3
/boardb/~Q1: EO1.6, HO18.9
/boardb/~Q2: E6.2, EO1.11
/boardb/~Q3: D19.9, E19.9, EO1.14, F7.9, F19.9
/boardb/~QQ2: D19.7, D19.10, E6.3
/boardb/~R: E5.1, EO4.9, F6.13
/boardb/~SELECT: E5.4, EO4.10, F6.9
/boardb/~WE: D22.10, D23.10, D24.10, F21_2.1, F23.1, H20.3
/boardc/Board C Top/CNTA0: F15_3.14, F19_3.13
/boardc/Board C Top/CNTA1: F15_3.13, F20_3.3
/boardc/Board C Top/CNTA2: F15_3.12, F20_3.6
/boardc/Board C Top/CNTA3: F15_3.11, F20_3.10
/boardc/Board C Top/CNTA4: F20_3.13, H15_3.14
/boardc/Board C Top/CNTA11: F19_3.10, H16_3.11
/boardc/Board C Top/CNTB3: F18_3.3, H17_3.11
/boardc/Board C Top/CNTB4: F18_3.6, H18_3.14
/boardc/Board C Top/CNTB5: F18_3.10, H18_3.13
/boardc/Board C Top/CNTB6: F18_3.13, H18_3.12
/boardc/Board C Top/CNTB7: F19_3.3, H18_3.11
/boardc/Board C Top/CNTB8: F19_3.6, H19_3.14
/boardc/Board C Top/L0: F15_3.3, F16_3.6
/boardc/Board C Top/L1: F15_3.4, F16_3.15
/boardc/Board C Top/L2: F15_3.5, F16_3.9
/boardc/Board C Top/L3: F15_3.6, F16_3.12
/boardc/Board C Top/L4: H15_3.3, H20_3.5
/boardc/Board C Top/L7: F16_3.2, H16_3.3
/boardc/Board C Top/L8: F16_3.19, H16_3.4
/boardc/Board C Top/L9: F16_3.5, H16_3.5
/boardc/Board C Top/L10: F16_3.16, H16_3.6
/boardc/Board C Top/M6: F19_3.11, H21_3.2
/boardc/Board C Top/M7: F19_3.14, H21_3.5
/boardc/Board C Top/N0: F17_3.2, H17_3.3
/boardc/Board C Top/N1: F17_3.19, H17_3.4
/boardc/Board C Top/N2: F17_3.5, H17_3.5
/boardc/Board C Top/N3: F17_3.16, H17_3.6
/boardc/Board C Top/N4: F17_3.6, H18_3.3
/boardc/Board C Top/N5: F17_3.15, H18_3.4
/boardc/Board C Top/N6: F17_3.9, H18_3.5
/boardc/Board C Top/N7: F17_3.12, H18_3.6
/boardc/Board C Top/Q0: F18_3.2, F21_3.2
/boardc/Board C Top/Q1: F18_3.11, F21_3.5
/boardc/Board C Top/Q2: F19_3.2, F21_3.7
/boardc/Board C Top/Q3: F19_3.5, F21_3.10
/boardc/Board C Top/Q4: F18_3.14, F21_3.12
/boardc/Board C Top/Q5: F18_3.5, F21_3.15
/boardc/Board C middle/CNTA3: F10_3.11, F13_3.3
/boardc/Board C middle/CNTA4: F9_3.14, F13_3.6
/boardc/Board C middle/CNTA5: F9_3.13, F13_3.10
/boardc/Board C middle/CNTA6: F9_3.12, F13_3.13
/boardc/Board C middle/CNTA7: F9_3.11, F12_3.3
/boardc/Board C middle/CNTA8: F8_3.14, F12_3.6
/boardc/Board C middle/CNTB3: F12_3.13, H10_3.11
/boardc/Board C middle/CNTB4: F12_3.10, H9_3.14
/boardc/Board C middle/CNTB5: H9_3.13, H12_3.3
/boardc/Board C middle/CNTB6: H9_3.12, H12_3.6
/boardc/Board C middle/CNTB7: H9_3.11, H12_3.13
/boardc/Board C middle/CNTB8: H8_3.14, H12_3.10
/boardc/Board C middle/L0: F10_3.3, F11_3.2
/boardc/Board C middle/L1: F10_3.4, F11_3.19
/boardc/Board C middle/L2: F10_3.5, F11_3.5
/boardc/Board C middle/L3: F10_3.6, F11_3.16
/boardc/Board C middle/L4: F9_3.3, F11_3.6
/boardc/Board C middle/L5: F9_3.4, F11_3.15
/boardc/Board C middle/L6: F9_3.5, F11_3.9
/boardc/Board C middle/L7: F9_3.6, F11_3.12
/boardc/Board C middle/M6: F12_3.11, H14_3.2
/boardc/Board C middle/M7: F12_3.14, H14_3.5
/boardc/Board C middle/N0: H10_3.3, H11_3.9
/boardc/Board C middle/N1: H10_3.4, H11_3.12
/boardc/Board C middle/N2: H10_3.5, H11_3.6
/boardc/Board C middle/N3: H10_3.6, H11_3.15
/boardc/Board C middle/N4: H9_3.3, H11_3.5
/boardc/Board C middle/N5: H9_3.4, H11_3.16
/boardc/Board C middle/N6: H9_3.5, H11_3.2
/boardc/Board C middle/N7: H9_3.6, H11_3.19
/boardc/Board C middle/Q0: F13_3.2, F14_3.2
/boardc/Board C middle/Q1: F13_3.5, F14_3.5
/boardc/Board C middle/Q2: F13_3.14, F14_3.7
/boardc/Board C middle/Q3: F12_3.5, F14_3.10
/boardc/Board C middle/Q4: F12_3.2, F14_3.12
/boardc/Board C middle/Q5: F13_3.11, F14_3.15
/boardc/board c bot/CNTA3: F5_3.11, FB1.3
/boardc/board c bot/CNTA4: F4_3.12, FB1.6
/boardc/board c bot/CNTA5: F4_3.13, FB1.10
/boardc/board c bot/CNTA6: F4_3.14, FB1.13
/boardc/board c bot/CNTA7: F4_3.11, F7_3.3
/boardc/board c bot/CNTA8: F3_3.14, F7_3.6
/boardc/board c bot/CNTB3: F7_3.13, H5.11
/boardc/board c bot/CNTB4: F7_3.10, H4.14
/boardc/board c bot/CNTB5: H4.13, H7_3.3
/boardc/board c bot/CNTB6: H4.12, H7_3.6
/boardc/board c bot/CNTB7: H4.11, H7_3.10
/boardc/board c bot/CNTB8: H3_3.14, H7_3.13
/boardc/board c bot/L0: F5_3.3, F6_3.2
/boardc/board c bot/L1: F5_3.4, F6_3.19
/boardc/board c bot/L2: F5_3.5, F6_3.5
/boardc/board c bot/L3: F5_3.6, F6_3.16
/boardc/board c bot/L4: F4_3.3, F6_3.6
/boardc/board c bot/L5: F4_3.4, F6_3.15
/boardc/board c bot/L6: F4_3.5, F6_3.9
/boardc/board c bot/L7: F4_3.6, F6_3.12
/boardc/board c bot/M6: F7_3.11, H2_3.2
/boardc/board c bot/M7: F7_3.14, H2_3.5
/boardc/board c bot/N0: H5.3, H6_3.9
/boardc/board c bot/N1: H5.4, H6_3.12
/boardc/board c bot/N2: H5.5, H6_3.6
/boardc/board c bot/N3: H5.6, H6_3.15
/boardc/board c bot/N4: H4.3, H6_3.5
/boardc/board c bot/N5: H4.4, H6_3.16
/boardc/board c bot/N6: H4.5, H6_3.2
/boardc/board c bot/N7: H4.6, H6_3.19
/boardc/board c bot/Q0: F2_3.2, FB1.2
/boardc/board c bot/Q1: F2_3.5, FB1.5
/boardc/board c bot/Q2: F2_3.7, FB1.14
/boardc/board c bot/Q3: F2_3.10, F7_3.5
/boardc/board c bot/Q4: F2_3.12, F7_3.2
/colmix/PALA0: DL22.4, EC22.8, EC24.8
/colmix/PALA1: DL22.7, EC22.7, EC24.7
/colmix/PALA2: DL22.9, EC22.6, EC24.6
/colmix/PALA3: DL22.12, EC22.5, EC24.5
/colmix/PALA4: DL23.4, EC22.4, EC24.4
/colmix/PALA5: DL23.7, EC22.3, EC24.3
/colmix/PALA6: DL23.9, EC22.2, EC24.2
/colmix/PALA7: DL23.12, EC22.1, EC24.1
/colmix/PALA8: DL24.4, EC22.23, EC24.23
/colmix/PALA9: DL24.7, EC22.22, EC24.22
/colmix/PALA10: DL24.9, EC22.19, EC24.19
/colmix/~OE: DL24.12, EC22.20, EC24.20
/gfxa/A0: B9.7, B10.7, DG9.7, EG9.9, FG7.2
/gfxa/A1: B9.6, B10.6, DG9.6, EG9.10, FG7.3
/gfxa/A2: B9.5, B10.5, DG9.5, EG9.11, FG7.4
/gfxa/A3: B9.4, B10.4, DG9.4, EG9.13, FG7.5
/gfxa/A4: B9.3, B10.3, DG9.3, EG9.14, FG7.6
/gfxa/A5: B9.25, B10.25, DG9.25, EG9.15, FG7.7
/gfxa/A6: B9.24, B10.24, DG9.24, EG9.16, FG7.8
/gfxa/A7: B9.21, B10.21, DG9.21, EG9.17, FG7.9
/gfxa/A8: B9.23, B10.23, DG9.23, EG10.9, HG7.2
/gfxa/A9: B9.2, B10.2, DG9.2, EG10.10, HG7.3
/gfxa/A10: B9.26, B10.26, DG9.26, EG10.11, HG7.4
/gfxa/D3: E11.3, EG10.13, HG7.5
/gfxa/D4: E11.4, EG10.14, HG7.6
/gfxa/D5: E11.6, EG10.15, HG7.7
/gfxa/D6: E11.11, EG10.16, HG7.8
/gfxa/D7: E11.13, EG10.17, HG7.9
/gfxa/I0A: A8.8, A11.2
/gfxa/I0B: A10.8, A11.5
/gfxa/I0D: A9.8, A11.11
/gfxa/I1A: A10.17, A11.3
/gfxa/I1B: A8.17, A11.6
/gfxa/I1D: A9.17, A11.10
/gfxa/S0: A8.1, A9.1, A10.1, F9.12
/gfxa/S1: A8.19, A9.19, A10.19, F9.6
/main/DDQ0: D21.2, D21.12
/main/DDQ2: D21.10, D21.13
/main/DQ0: F15.2, F15.12
/main/DQ2: F15.10, F15.13
/main/FC0: FU12.1, J11.28
/main/FC1: FU12.2, J11.27
/main/FC2: FU12.3, J11.26
/main/Q3: D20.1, D21.15
/main/QQ3: F15.15, F16.1
/main/RAMCS: J8.26, J15.2, K8.26
/main/~RAMCS: J15.1, K13.12
/main/~ROM0CS: J7.20, K7.20, K13.13
/main/~ROM1CS: J6.20, J18.8, K6.20
/main/~VMA: J11.19, K14.4
/main/~VPA: J11.21, J17.3
/memories/ADI0: A12.7, D10.11
/memories/ADI1: A12.13, D10.12
/memories/ADI2: A12.6, D10.13
/memories/ADI3: A12.14, D10.15
/memories/ADI4: A12.5, D10.16
/memories/ADI5: A12.15, D10.17
/memories/ADI6: A12.4, D10.18
/memories/ADI7: A12.16, D10.19
/memories/AIO0: A17.7, D17.11
/memories/AIO1: A17.13, D17.12
/memories/AIO2: A17.6, D17.13
/memories/AIO3: A17.14, D17.15
/memories/AIO4: A17.5, D17.16
/memories/AIO5: A17.15, D17.17
/memories/AIO6: A17.4, D17.18
/memories/AIO7: A17.16, D17.19
/memories/BIO0: A18.7, C18.11
/memories/BIO1: A18.13, C18.12
/memories/BIO2: A18.6, C18.13
/memories/BIO3: A18.14, C18.15
/memories/BIO4: A18.5, C18.16
/memories/BIO5: A18.15, C18.17
/memories/BIO6: A18.4, C18.18
/memories/BIO7: A18.16, C18.19
/memories/CIO0: A19.7, D18.11
/memories/CIO1: A19.13, D18.12
/memories/CIO2: A19.6, D18.13
/memories/CIO3: A19.14, D18.15
/memories/CIO4: A19.5, D18.16
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
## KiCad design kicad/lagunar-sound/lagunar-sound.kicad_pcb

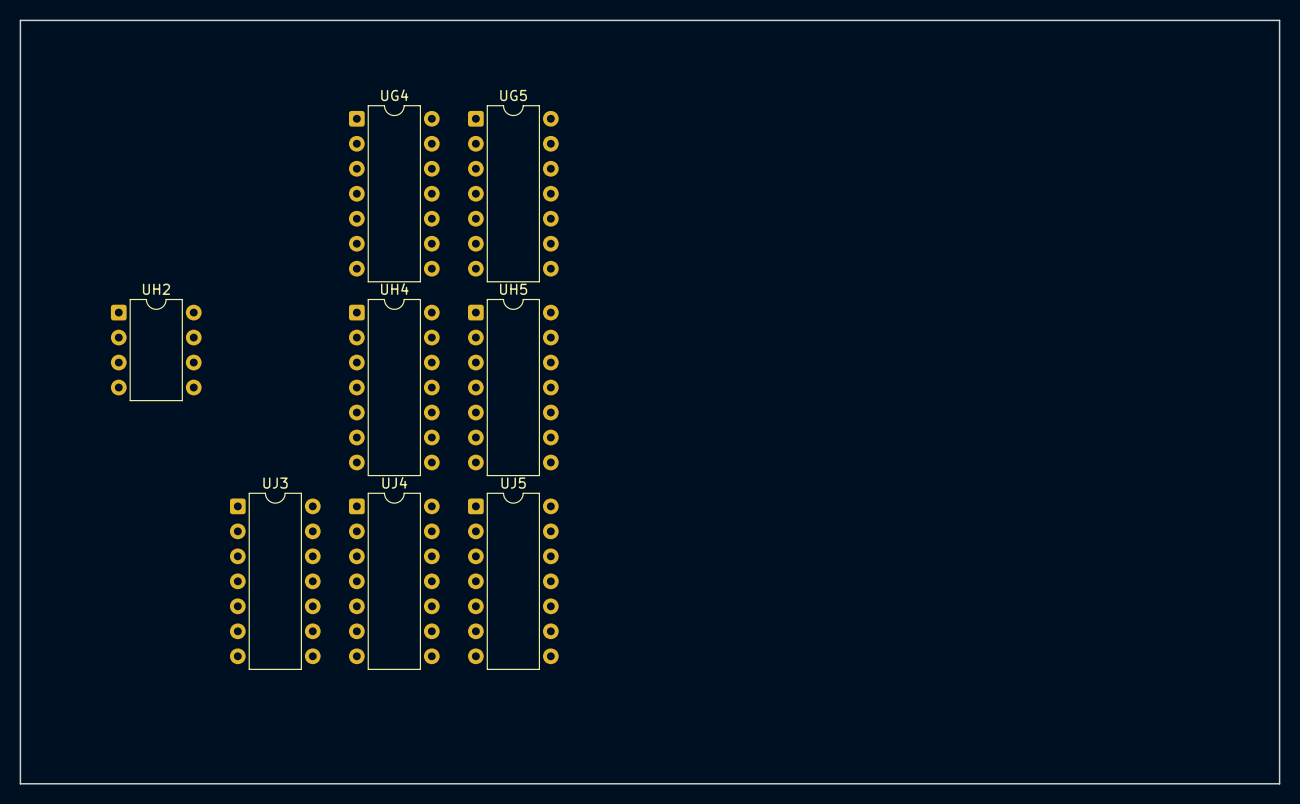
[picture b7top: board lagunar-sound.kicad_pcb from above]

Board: 2 copper layers, 128.0 x 77.6 mm, 8 parts (0 on the bottom side), 12 nets, no tracks yet.

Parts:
UG4, UG5: CD4016; DIP-14_W7.62mm
UH2: MC3340; DIP-8_W7.62mm
UH4, UH5: LM3900; DIP-14_W7.62mm
UJ3, UJ5: LM3900; DIP-14_W7.62mm
UJ4: CD4016; DIP-14_W7.62mm

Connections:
+5V: UG4.14, UG5.14, UH4.14, UH5.14, UJ3.14, UJ4.14, UJ5.14
GND: UG4.7, UG5.1, UG5.7, UH2.3, UH4.7, UH5.7, UJ3.7, UJ4.7, UJ5.7
unnamed: UG4.8, UH5.4
unnamed: UG5.3, UG5.8
unnamed: UG4.4, UH4.10
unnamed: UJ3.5, UJ4.13
unnamed: UJ3.10, UJ4.5
unnamed: UJ4.12, UJ5.5
unnamed: UG5.4, UH5.11
unnamed: UJ3.2, UJ4.2
unnamed: UJ3.13, UJ4.3
unnamed: UJ4.11, UJ5.2
